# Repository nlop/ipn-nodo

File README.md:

# ipn-nodo

Project files for the project _Remote Plant Monitoring System_ (TT2020-B031).
Includes both the ESP32's source code and KiCad files for the circuit and PCB
designs.

# Documents
- [Report (spanish only)](doc/articulo_tt2020b031.pdf)
- [Circuit schematic](doc/schematic.pdf)
- [Building instructions (spanish only)](doc/instructions/)

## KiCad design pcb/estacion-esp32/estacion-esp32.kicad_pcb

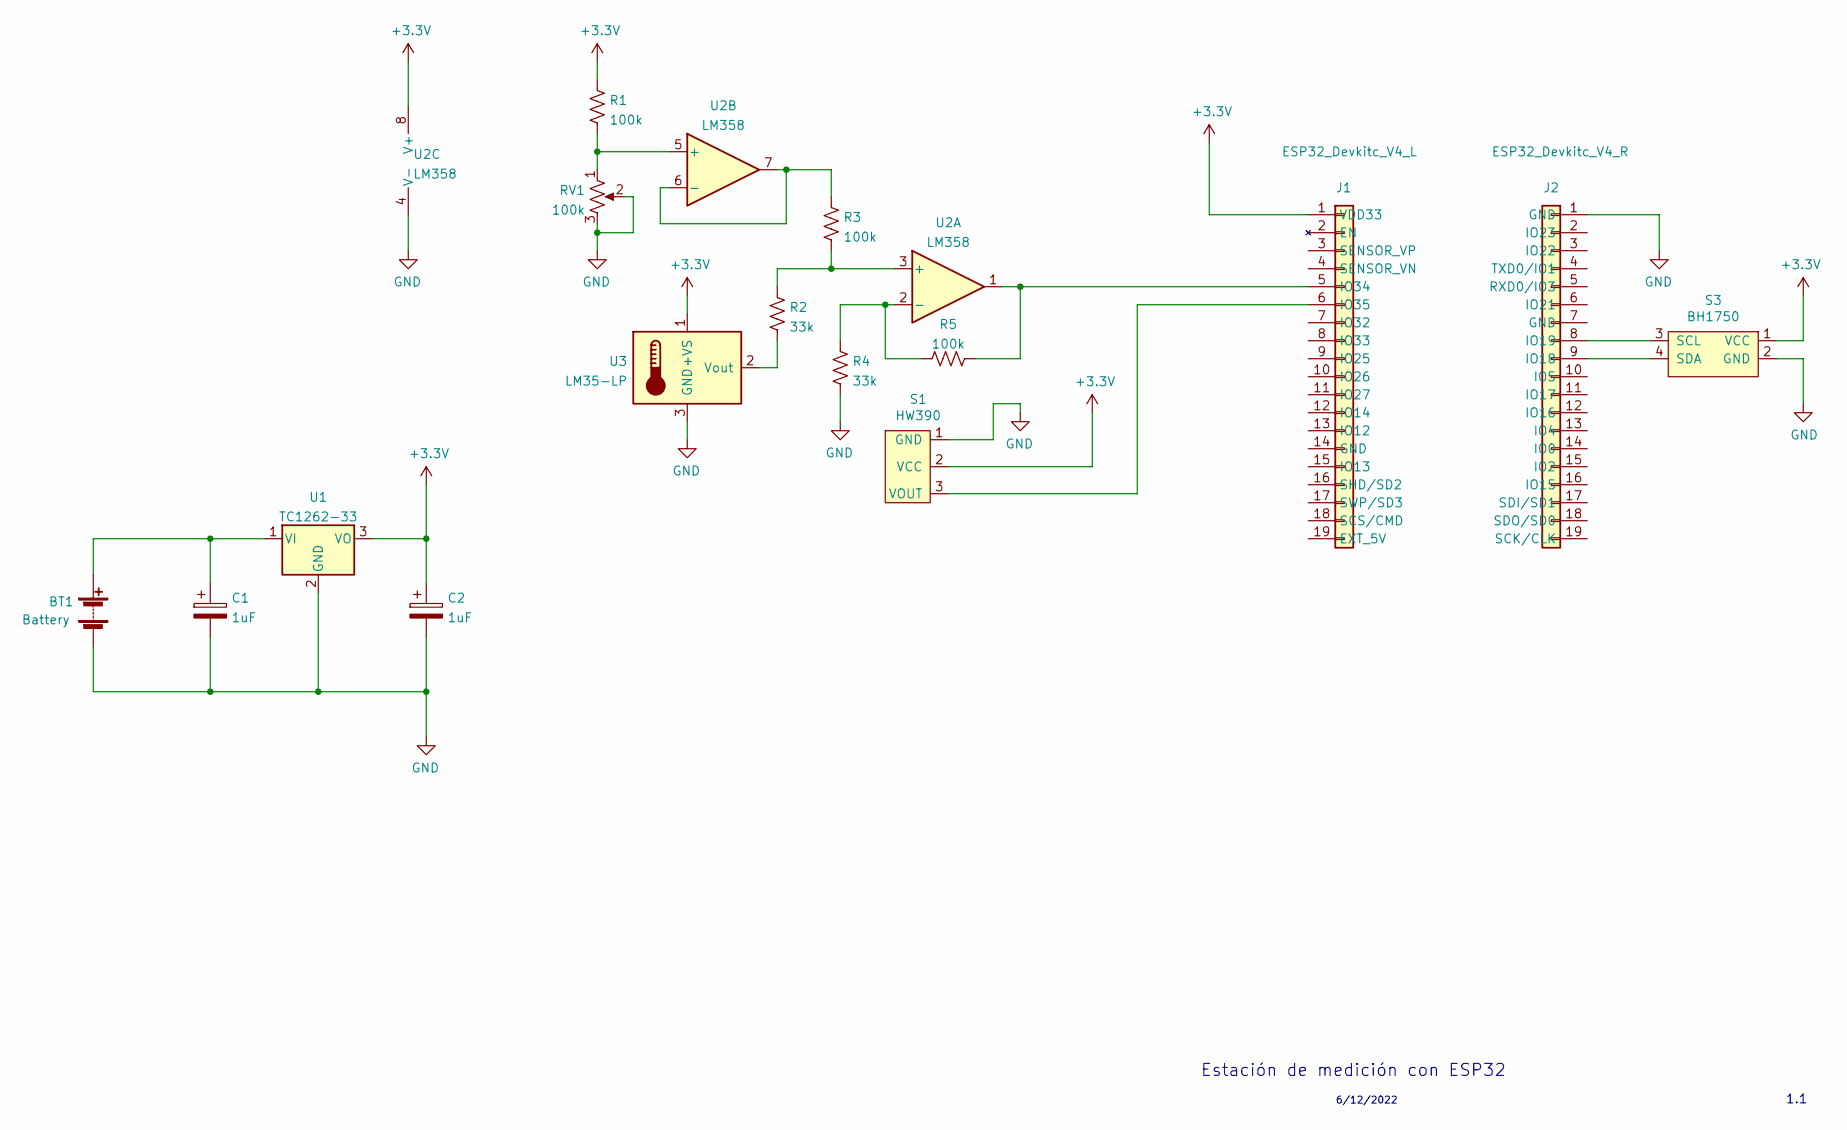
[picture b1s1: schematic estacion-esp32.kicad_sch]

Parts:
BT1: Battery; JST_PH_B2B-PH-K_1x02_P2.00mm_Vertical
C1, C2: 1uF; CP_Radial_D4.0mm_P2.00mm
J1: ESP32_Devkitc_V4_L; PinSocket_1x19_P2.54mm_Vertical
J2: ESP32_Devkitc_V4_R; PinSocket_1x19_P2.54mm_Vertical
R1, R3, R5: 100k; R_Axial_DIN0207_L6.3mm_D2.5mm_P7.62mm_Horizontal
R2, R4: 33k; R_Axial_DIN0207_L6.3mm_D2.5mm_P7.62mm_Horizontal
RV1: 100k; Potentiometer_Vishay_T73XW_Horizontal
S1: HW390; PinHeader_1x03_P2.54mm_Vertical
S3: BH1750; PinSocket_1x04_P2.54mm_Vertical
U1: TC1262-33; TO-220-3_Vertical
U2: LM358; DIP-8_W7.62mm
U3: LM35-LP; TO-92_HandSolder

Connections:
+3V3: C2.1, J1.1 (VDD33), R1.1, S1.2 (VCC), S3.1 (VCC), U1.3 (VO), U2.8 (V+), U3.1 (+VS)
GND: BT1.2 (-), C1.2, C2.2, J2.1 (GND), R4.2, RV1.2, RV1.3, S1.1 (GND), S3.2 (GND), U1.2 (GND), U2.4 (V-), U3.3 (GND)
unnamed: BT1.1 (+), C1.1, U1.1 (VI)
unnamed: J1.5 (IO34), R5.2, U2.1
unnamed: J1.6 (IO35), S1.3 (VOUT)
unnamed: J2.8 (IO19), S3.3 (SCL)
unnamed: J2.9 (IO18), S3.4 (SDA)
unnamed: R1.2, RV1.1, U2.5 (+)
unnamed: R2.1, R3.1, U2.3 (+)
unnamed: R2.2, U3.2 (Vout)
unnamed: R3.2, U2.6 (-), U2.7
unnamed: R4.1, R5.1, U2.2 (-)

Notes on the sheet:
6/12/2022
1.1
Estación de medición con ESP32

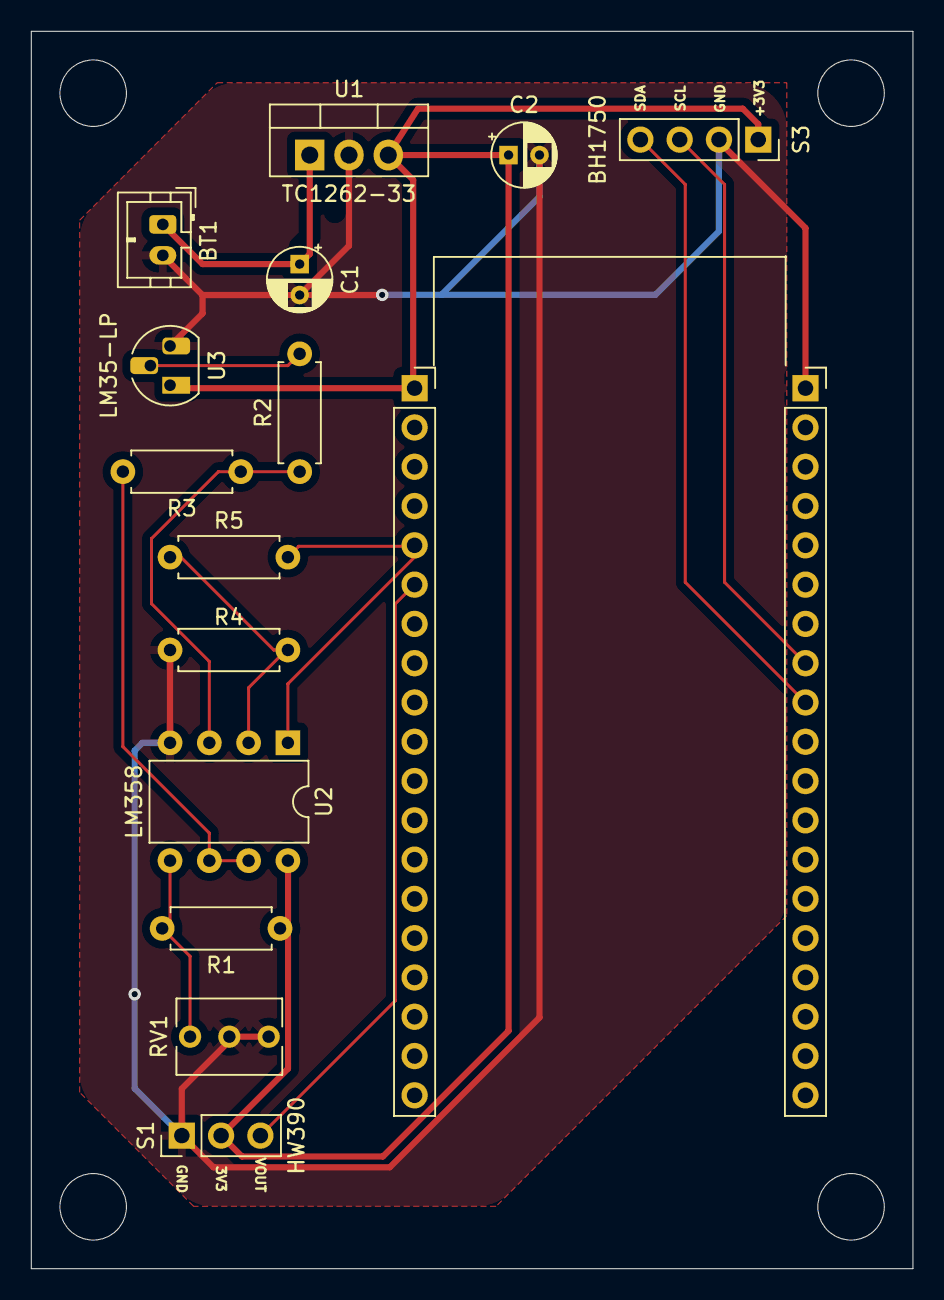
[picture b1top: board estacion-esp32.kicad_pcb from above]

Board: 2 copper layers, 57.0 x 80.0 mm, 16 parts (0 on the bottom side), 12 nets.

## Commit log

2021-10-26 Script para compilar, gitignore y base para la configuración del SDK
2021-10-28 Funcionalidad de servidor usando un perfil BLE-GATT - Se tiene la capacidad de arrancar el servicio junto con el task de medición y se pueden exponer los valores a partir de características estableci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
2021-10-29 * Nueva dirección del perfil GATT * Descriptores de formato para los campos del servicio * Campo de apariencia como "Multisensor" (BT SIG)
2021-10-29 Renombrar las constantes para identificar los namespaces para guardar datos de AP y Token. Sustituye los nombres que hacían referencia a una partición en lugar de un namespace
2021-10-29 * Refactorización las constantes usadas para establecer las URL, puertos, etc de los servicios web * Modificación de las estructuras de configuración para utilizar un esquema mas detallado para señal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
2021-10-29 Nueva partición de la memoria flash con partición SPIFFS y 2MB para guardar la aplicación
2021-11-05 * Cambio de nombre para callback * Eliminación de mem_release en la secuencia de inicio del controlador Bluetooth * Timeout para reintentar el envío del token temporal
2021-11-05 Avance de nueva secuencia de inicio
2021-11-05 fix: Llaves de namespace duplicadas
2021-11-06 Avance en secuencia de inicio BLE * Capacidad de arrancar el dispositivo en modo WiFi y BLE * Manejo de mensajes en SPP para arrancar el dispositivo * Simplificación de bits del semáforo: WIFI_OK y G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
2021-11-11 Función para deshabilitar el controlador WiFi
2021-11-11 Multiples ajustes * Eliminación de asignación de byte final en get_mac() * Comas alineadas en custom_part.csv * Encapsular variables utilizadas cuando se habilita el TSL2561, dentro de los bloques #I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
2021-11-11 Funcionalidad para activar el cliente GATT a traves de mensajes del WebSocket - El prototipo puede inicializar el módulo BT/BLE y alzar un cliente GATT, así como buscar un dispositivo, dada una direc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
2021-11-12 Funciones básicas de SPIFFS Implementación de las funciones de creación y obtención de registros a partir de un archivo almacenado en la partición de datos con un sistema de archivos SPIFFS, utilizad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
2021-11-12 Registro de servidores GATT - Funciones para guardar la dirección de los servidores GATT que han sido registrados a partir de los mensajes 'esp-dev-discovery'. Adicionalmente, se hace lecutra de esta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
2021-11-14 Avances de modificación al cliente de GATT para diferentes conexiones
2021-11-15 Reporte de mediciones en stand-by con nodos BLE * Conexión a un servidor GATTS con dirección explicita * Modificación del módulo GATTC para considerar los casos de inicialización y medición normal * 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
2021-11-16 Primera version de la implementación de la estación con BLE * Tiene la capacidad de recibir mensajes desde WebSocket para encontar algún dispositivo BLE-GATTS que ya se encuentre realizando advertisi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
2021-11-20 Soporte para sensor BH1750
2021-11-20 Opción de configuración para el intervalo del ping en WebSocket
2021-11-20 Actualización del README
2021-11-26 Funcionalidad de token con websocket
2021-11-28 Ajustes para realizar el intercambio de token con el servidor
2021-11-28 Uso de parámetros de configuración para generar rutas del servidor
2021-11-30 Arreglo de rutas para Websocket
2021-11-30 Primera calibración del sensor de humedad
2021-12-01 Avance de cambios para implementar el módulo de control
2021-12-01 Temperatura como valor decimal
2021-12-01 Reducción de frecuencia en procesador/modem sleep WiFi
2021-12-04 Nueva escala para humedad/Aumentar buffer para arreglo de mediciones
2021-12-04 Primera refactorización Movimiento de código y archivos * División de nodo_web entre la funcionalidad de Websocket y cliente HTTP. Creación de la carpeta 'web' para este tipo de código * Movimiento d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
2021-12-04 Segunda refactorización Nuevos directorios y algunas funciones * Se comenzó la transición de la funcionalidad de nuevo nodo periférico a measure.c, donde se llevará a cabo el control del nodo * Nuevo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
2021-12-07 Mover archivos de constantes para eventos y tipo de nodo a un solo directorio
2021-12-07 Sacar dev_addr de measure_vector_t
2021-12-07 Arreglos para cumplir con el nuevo formato de mensajes JSON
2021-12-08 Soporte de instance_id para GATT (cliente y servidor) Implementación de una secuencia de 16 bytes para comprobar la conexión con el nodo al momento de provisionar un nuevo nodo en modo BLE
2021-12-13 Ajustes para agregar nodos periféricos con la app/Otros ajustes
2021-12-14 Semáforo para bloquear la lectura de características por el cliente GATT
2021-12-18 Servidor GATT: Migración de tipos de datos
2021-12-18 Migración de tipos de datos Cliente web y GATT - Cambio de tipos de datos para cliente GATT y funciones utilizadas para el cliente web (websocket). - Semáforo para controlar las llamadas al cliente G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
2021-12-18 Fin del soporte para sensor TSL2561
2021-12-23 Grafica con puntos de calibración para LM35
2022-01-03 Primera version del gráfico de error para sensor de temperatura
2022-01-04 Datos de calibración (LM35 & HW390)
2022-01-04 Gráfica de interpolación para HW390 y calibración
2022-01-05 Graficos nuevos (LM35, HW390, Wifi, BLE)
    Scripts para los graficos del sensor LM35 y HW390
    Gráficos de los controladores BLE y WiFi
2022-01-05 Graficas con inset para LM35
2022-01-05 Tabla con desviación para LM35 y HW390
2022-01-09 Fix para problema de aprovisionamiento de nuevo nodo
2022-01-09 Ordenar APs por RSSI
2022-01-09 Escala logarítmica para la humedad
2022-01-09 Datos finales de calibración y caracterización de señales
2022-01-09 PCB versión 1.1
2022-01-14 Graficas con inset para LM35 Agregar inset a gráficas de calibración para el sensor LM35
2022-01-20 Dump final
2023-01-28 Update README and add documentation
2023-01-28 Fix wrong image extension
